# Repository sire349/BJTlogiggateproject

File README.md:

# BJTlogiggateproject
aims to create faster and more energy efficient BJT logic gates and tries to maintain itself cooler than 30°C

Currently testing with PCB designing, I'm trying to build a 4bit adder and turn it into a fully working pCB, once I know how to correctly make,
I'll try to bring my logic up to faster speeds.
I made this project because I love transistors and how PCs work, so I decided to exeperience myself in first person.

Using my preject is actually very simple, it's just a 4bit adder, you can add 4bit numbers together to gain the sum of them! No further knowledge is required.
You only need to know basic transistor logic and how binary works.

Step 1
using LTspice for simulating higher speeds

Step2
Designing a working PCB

Step3
Having a working PCB to then upgrade it

BOM link
https://github.com/sire349/BJTlogiggateproject/blob/main/bom.csv

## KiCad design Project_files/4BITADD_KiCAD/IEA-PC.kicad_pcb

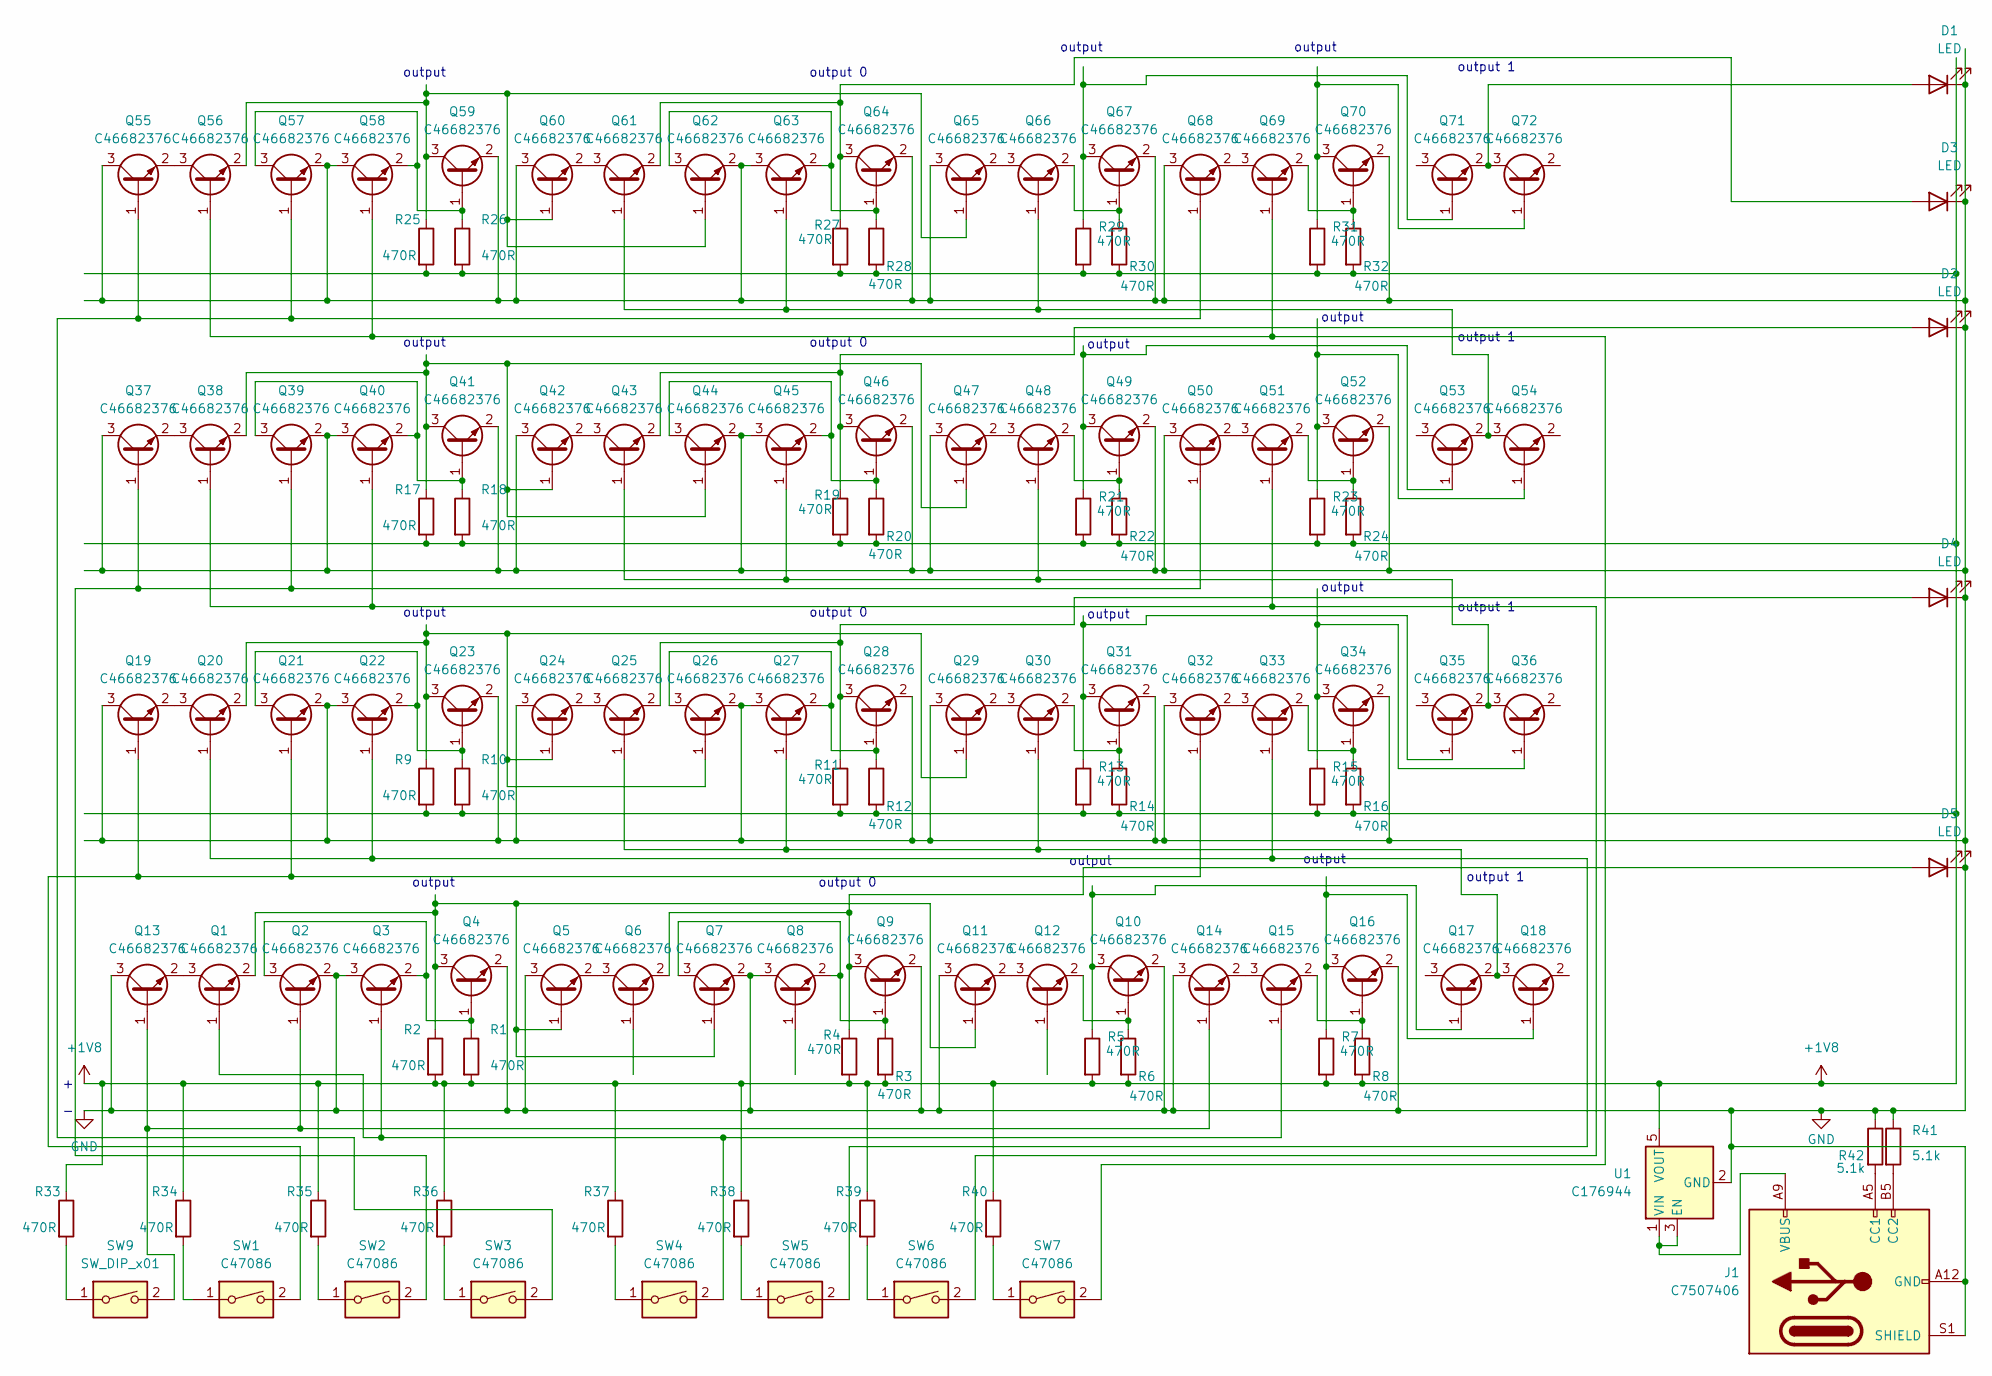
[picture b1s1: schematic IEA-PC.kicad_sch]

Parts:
D1, D2, D3, D4, D5: LED; LED_0603_1608Metric
J1: C7507406; USB_C_Receptacle_GCT_USB4135-GF-A_6P_TopMnt_Horizontal
Q1, Q2, Q3, Q4, Q5, Q6, Q7, Q8, Q9, Q10, Q11, Q12, Q13, Q14, Q15, Q16, Q17, Q18, Q19, Q20, Q21, Q22, Q23, Q24, Q25, Q26, Q27, Q28, Q29, Q30, Q31, Q32, Q33, Q34, Q35, Q36, Q37, Q38, Q39, Q40, Q41, Q42, Q43, Q44, Q45, Q46, Q47, Q48, Q49, Q50, Q51, Q52, Q53, Q54, Q55, Q56, Q57, Q58, Q59, Q60, Q61, Q62, Q63, Q64, Q65, Q66, Q67, Q68, Q69, Q70, Q71, Q72: C46682376; SOT-23
R1, R2, R3, R4, R5, R6, R7, R8, R9, R10, R11, R12, R13, R14, R15, R16, R17, R18, R19, R20, R21, R22, R23, R24, R25, R26, R27, R28, R29, R30, R31, R32, R33, R34, R35, R36, R37, R38, R39, R40: 470R; R_0603_1608Metric
R41, R42: 5.1k; R_0603_1608Metric
SW1, SW2, SW3, SW4, SW5, SW6, SW7: C47086; SW_DIP_SPSTx01_Slide_6.7x4.1mm_W8.61mm_P2.54mm_LowProfile
SW9: SW_DIP_x01; SW_DIP_SPSTx01_Slide_6.7x4.1mm_W8.61mm_P2.54mm_LowProfile
U1: C176944; SOT-23-5

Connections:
+1V8: R1.2, R2.2, R3.2, R4.2, R5.2, R6.2, R7.2, R8.2, R9.2, R10.2, R11.2, R12.2, R13.2, R14.2, R15.2, R16.2, R17.2, R18.2, R19.2, R20.2, R21.2, R22.2, R23.2, R24.2, R25.2, R26.2, R27.2, R28.2, R29.2, R30.2, R31.2, R32.2, R33.1, R34.1, R35.1, R36.1, R37.1, R38.1, R39.1, R40.1, U1.5 (VOUT)
GND: D1.1 (K), D2.1 (K), D3.1 (K), D4.1 (K), D5.1 (K), J1.A12 (GND), J1.B12 (GND), J1.S1 (SHIELD), Q2.2 (E), Q3.3 (C), Q4.2 (E), Q5.3 (C), Q7.2 (E), Q8.3 (C), Q9.2 (E), Q10.2 (E), Q11.3 (C), Q13.3 (C), Q14.3 (C), Q16.2 (E), Q19.3 (C), Q21.2 (E), Q22.3 (C), Q23.2 (E), Q24.3 (C), Q26.2 (E), Q27.3 (C), Q28.2 (E), Q29.3 (C), Q31.2 (E), Q32.3 (C), Q34.2 (E), Q37.3 (C), Q39.2 (E), Q40.3 (C), Q41.2 (E), Q42.3 (C), Q44.2 (E), Q45.3 (C), Q46.2 (E), Q47.3 (C), Q49.2 (E), Q50.3 (C), Q52.2 (E), Q55.3 (C), Q57.2 (E), Q58.3 (C), Q59.2 (E), Q60.3 (C), Q62.2 (E), Q63.3 (C), Q64.2 (E), Q65.3 (C), Q67.2 (E), Q68.3 (C), Q70.2 (E), R41.1, R42.1, U1.2 (GND)
unnamed: D1.2 (A), Q71.2 (E), Q72.3 (C)
unnamed: D2.2 (A), Q43.2 (E), Q46.3 (C), R19.1
unnamed: D3.2 (A), Q61.2 (E), Q64.3 (C), R27.1
unnamed: D4.2 (A), Q25.2 (E), Q28.3 (C), R11.1
unnamed: D5.2 (A), Q6.2 (E), Q9.3 (C), R4.1
unnamed: J1.A5 (CC1), R42.2
unnamed: J1.B5 (CC2), R41.2
unnamed: Q1.1 (B), Q3.1 (B), Q15.1 (B), SW4.2
unnamed: Q1.3 (C), Q13.2 (E)
unnamed: Q1.2 (E), Q4.3 (C), Q5.1 (B), Q7.1 (B), Q11.1 (B), R2.1
unnamed: Q2.3 (C), Q3.2 (E), Q4.1 (B), R1.1
unnamed: Q5.2 (E), Q6.3 (C)
unnamed: Q7.3 (C), Q8.2 (E), Q9.1 (B), R3.1
unnamed: Q10.1 (B), Q12.2 (E), R6.1
unnamed: Q10.3 (C), Q17.1 (B), R5.1
unnamed: Q11.2 (E), Q12.3 (C)
unnamed: Q2.1 (B), Q13.1 (B), Q14.1 (B), SW9.2
unnamed: Q14.2 (E), Q15.3 (C)
unnamed: Q15.2 (E), Q16.1 (B), R8.1
unnamed: Q16.3 (C), Q18.1 (B), R7.1
unnamed: Q17.2 (E), Q18.3 (C), Q25.1 (B), Q27.1 (B), Q30.1 (B)
unnamed: Q19.1 (B), Q21.1 (B), Q32.1 (B), SW1.2
unnamed: Q19.2 (E), Q20.3 (C)
unnamed: Q20.1 (B), Q22.1 (B), Q33.1 (B), SW5.2
unnamed: Q20.2 (E), Q23.3 (C), Q24.1 (B), Q26.1 (B), Q29.1 (B), R9.1
unnamed: Q21.3 (C), Q22.2 (E), Q23.1 (B), R10.1
unnamed: Q24.2 (E), Q25.3 (C)
unnamed: Q26.3 (C), Q27.2 (E), Q28.1 (B), R12.1
unnamed: Q29.2 (E), Q30.3 (C)
unnamed: Q30.2 (E), Q31.1 (B), R14.1
unnamed: Q31.3 (C), Q35.1 (B), R13.1
unnamed: Q32.2 (E), Q33.3 (C)
unnamed: Q33.2 (E), Q34.1 (B), R16.1
unnamed: Q34.3 (C), Q36.1 (B), R15.1
unnamed: Q35.2 (E), Q36.3 (C), Q43.1 (B), Q45.1 (B), Q48.1 (B)
unnamed: Q37.1 (B), Q39.1 (B), Q50.1 (B), SW2.2
unnamed: Q37.2 (E), Q38.3 (C)
unnamed: Q38.1 (B), Q40.1 (B), Q51.1 (B), SW6.2
unnamed: Q38.2 (E), Q41.3 (C), Q42.1 (B), Q44.1 (B), Q47.1 (B), R17.1
unnamed: Q39.3 (C), Q40.2 (E), Q41.1 (B), R18.1
unnamed: Q42.2 (E), Q43.3 (C)
unnamed: Q44.3 (C), Q45.2 (E), Q46.1 (B), R20.1
unnamed: Q47.2 (E), Q48.3 (C)
unnamed: Q48.2 (E), Q49.1 (B), R22.1
unnamed: Q49.3 (C), Q53.1 (B), R21.1
unnamed: Q50.2 (E), Q51.3 (C)
unnamed: Q51.2 (E), Q52.1 (B), R24.1
unnamed: Q52.3 (C), Q54.1 (B), R23.1
unnamed: Q53.2 (E), Q54.3 (C), Q61.1 (B), Q63.1 (B), Q66.1 (B)
unnamed: Q55.1 (B), Q57.1 (B), Q68.1 (B), SW3.2
unnamed: Q55.2 (E), Q56.3 (C)
unnamed: Q56.1 (B), Q58.1 (B), Q69.1 (B), SW7.2
unnamed: Q56.2 (E), Q59.3 (C), Q60.1 (B), Q62.1 (B), Q65.1 (B), R25.1
unnamed: Q57.3 (C), Q58.2 (E), Q59.1 (B), R26.1
unnamed: Q60.2 (E), Q61.3 (C)
unnamed: Q62.3 (C), Q63.2 (E), Q64.1 (B), R28.1
unnamed: Q65.2 (E), Q66.3 (C)
unnamed: Q66.2 (E), Q67.1 (B), R30.1
unnamed: Q67.3 (C), Q71.1 (B), R29.1
unnamed: Q68.2 (E), Q69.3 (C)
unnamed: Q69.2 (E), Q70.1 (B), R32.1
unnamed: Q70.3 (C), Q72.1 (B), R31.1
unnamed: R33.2, SW9.1
unnamed: R34.2, SW1.1
unnamed: R35.2, SW2.1
unnamed: R36.2, SW3.1
unnamed: R37.2, SW4.1
unnamed: R38.2, SW5.1
unnamed: R39.2, SW6.1
unnamed: R40.2, SW7.1
unnamed: J1.A9 (VBUS), J1.B9 (VBUS), U1.1 (VIN), U1.3 (EN)

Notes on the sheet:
output
output 1
output 0

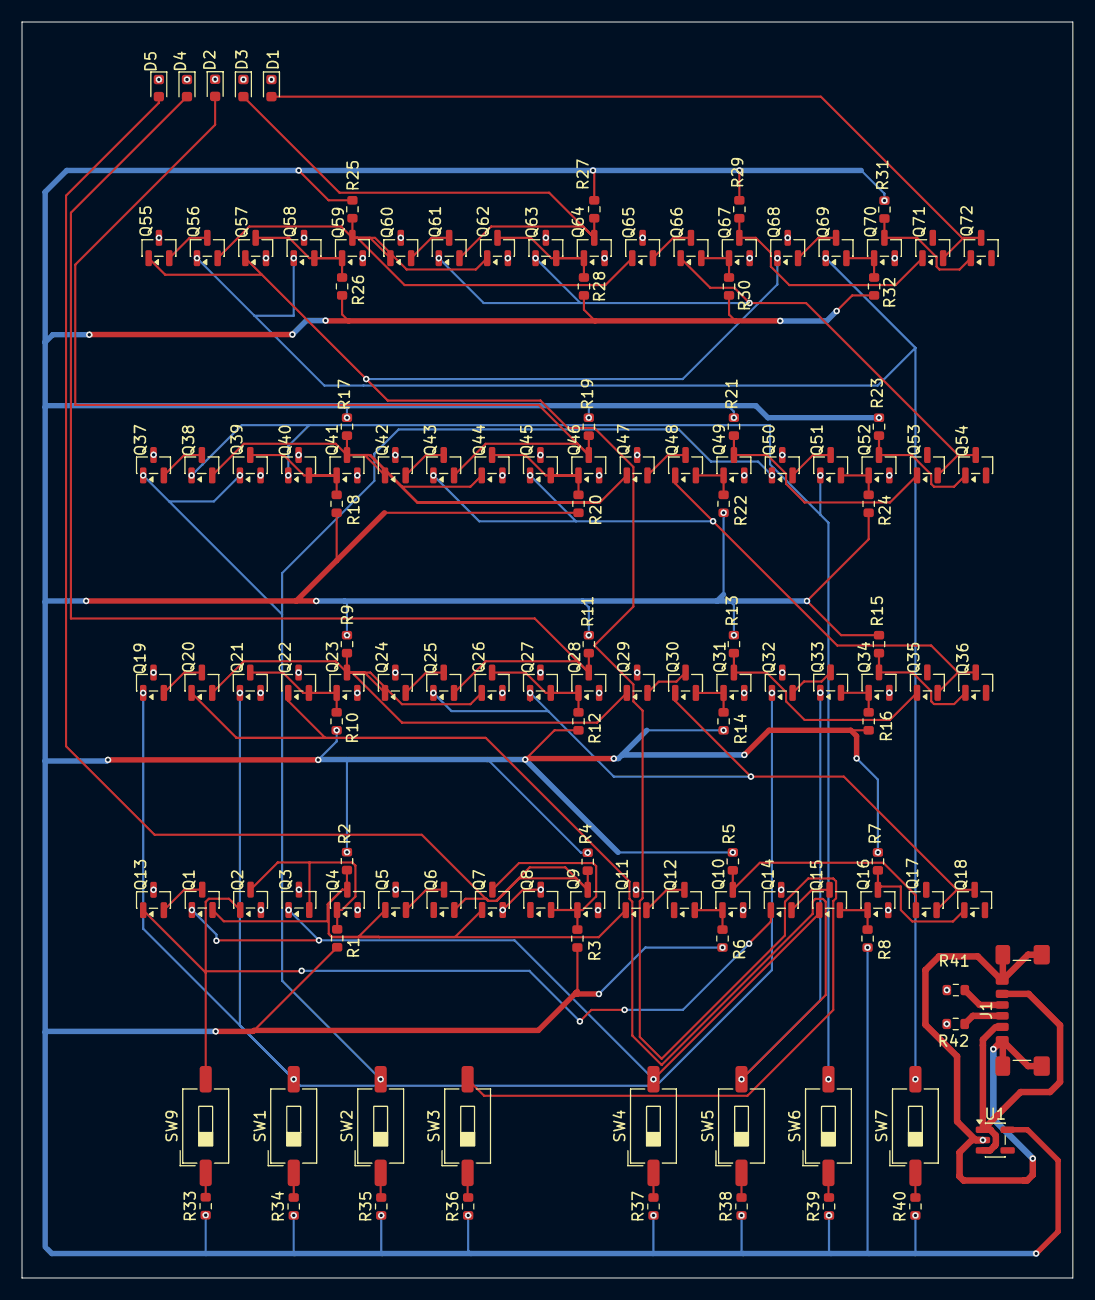
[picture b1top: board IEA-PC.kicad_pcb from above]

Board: 2 copper layers, 96.7 x 115.6 mm, 129 parts (0 on the bottom side), 73 nets.

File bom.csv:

Designator,Footprint,Quantity,Value,LCSC Part #
"D1, D2, D3, D4, D5",0603,5,LED,
J1,USB_C_Receptacle_GCT_USB4135-GF-A_6P_TopMnt_Horizontal,1,C7507406,
"Q1, Q10, Q11, Q12, Q13, Q14, Q15, Q16, Q17, Q18, Q19, Q2, Q20, Q21, Q22, Q23, Q24, Q25, Q26, Q27, Q28, Q29, Q3, Q30, Q31, Q32, Q33, Q34, Q35, Q36, Q37, Q38, Q39, Q4, Q40, Q41, Q42, Q43, Q44, Q45, Q46, Q47, Q48, Q49, Q5, Q50, Q51, Q52, Q53, Q54, Q55, Q56, Q57, Q58, Q59, Q6, Q60, Q61, Q62, Q63, Q64, Q65, Q66, Q67, Q68, Q69, Q7, Q70, Q71, Q72, Q8, Q9",SOT-23,72,C46682376,
"R1, R10, R11, R12, R13, R14, R15, R16, R17, R18, R19, R2, R20, R21, R22, R23, R24, R25, R26, R27, R28, R29, R3, R30, R31, R32, R33, R34, R35, R36, R37, R38, R39, R4, R40, R5, R6, R7, R8, R9",0603,40,470R,
"R41, R42",0603,2,5.1k,
"SW1, SW2, SW3, SW4, SW5, SW6, SW7, SW9",SW_DIP_SPSTx01_Slide_6.7x4.1mm_W8.61mm_P2.54mm_LowProfile,8,C47086,
U1,SOT-23-5,1,C176944,

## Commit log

2026-01-16 Create LICENSE
2026-01-16 Add CERN-OHL-S license
2026-01-16 Update README.md
    detailed description of my project
2026-01-17 Add files via upload
    This is my NAND gate at 10GHz in LTspice, Tr and Tf at 10p while Ton at 40p and Tperiod at 100p, the power usage per transistor is roughly 0.8mA and the sum is 1.6mA per NAND gate. INPUT and VCC were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
2026-01-17 Rename Screenshot 2026-01-17 180739.png to NAND gate picture
2026-01-17 Add files via upload
    NAND gate picture with graph. 10GHz, 0.8V, 1.6mA per switch.
2026-01-17 Add files via upload
    NAND gate, 10Ghz, 0.8V, ca3.8mA per switch
2026-01-25 AND gate topography, tested on breadboard to verify the boolean logic correctness
2026-01-25 XOR gate topography, tested on breadboard to verify boolean logic correctness
2026-01-31 Add files via upload
    this is an XOR gate I made, tested at 1KHz, it works without any problem!
2026-04-03 Create 0
2026-04-03 Rename Electrical scheme.png to Screenshots_3d_images/Electrical scheme.png
2026-04-03 Rename IEA-PC.png to Screenshots_3d_images/IEA-PC.png
2026-04-03 Rename PCB wiring image.png to Screenshots_3d_images/PCB wiring image.png
2026-04-03 Rename Screenshot 2026-03-24 233957.png to Screenshots_3d_images/Screenshot 2026-03-24 233957.png
2026-04-03 Rename Screenshot 2026-03-24 233945.png to Screenshots_3d_images/Screenshot 2026-03-24 233945.png
2026-04-03 Rename IEA-PC.step to Project_files/IEA-PC.step
2026-04-03 Rename IEA-PC.zip to Project_files/IEA-PC.zip
2026-04-03 Create 01
2026-04-03 Rename Project_files/IEA-PC.step to Project_files/4BITADD_KiCAD/IEA-PC.step
